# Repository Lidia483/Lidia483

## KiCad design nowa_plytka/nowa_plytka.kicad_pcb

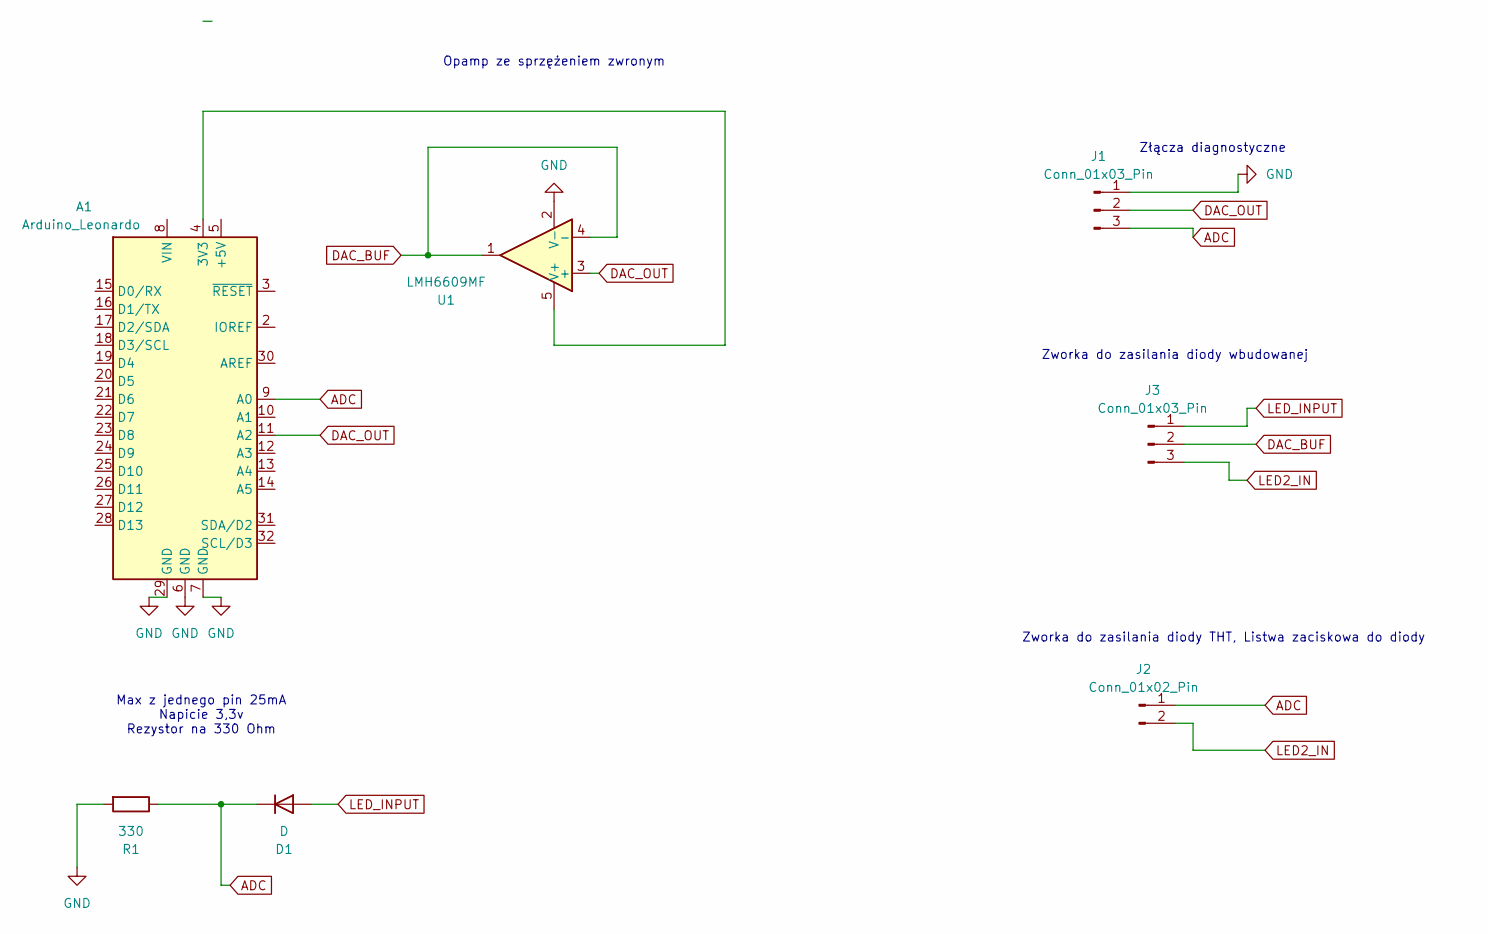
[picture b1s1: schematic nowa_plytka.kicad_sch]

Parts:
A1: Arduino_Leonardo; Arduino_UNO_R3
D1: D; D_1206_3216Metric
J1, J3: Conn_01x03_Pin; PinHeader_1x03_P2.54mm_Vertical
J2: Conn_01x02_Pin; PinHeader_1x02_P2.54mm_Vertical
R1: 330; R_1206_3216Metric
U1: LMH6609MF; SOT-23-5

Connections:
ADC: A1.9 (A0), D1.1 (K), J1.3, J2.1, R1.1
DAC_BUF: J3.2, U1.1, U1.4 (-)
DAC_OUT: A1.11 (A2), J1.2, U1.3 (+)
GND: A1.6 (GND), A1.7 (GND), A1.29 (GND), J1.1, R1.2, U1.2 (V-)
LED2_IN: J2.2, J3.3
LED_INPUT: D1.2 (A), J3.1
unnamed: A1.4 (3V3), U1.5 (V+)

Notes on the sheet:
Opamp ze sprzężeniem zwronym
Zworka do zasilania diody wbudowanej
Max z jednego pin 25mA Napicie 3,3v Rezystor na 330 Ohm
Złącza diagnostyczne
Zworka do zasilania diody THT, Listwa zaciskowa do diody

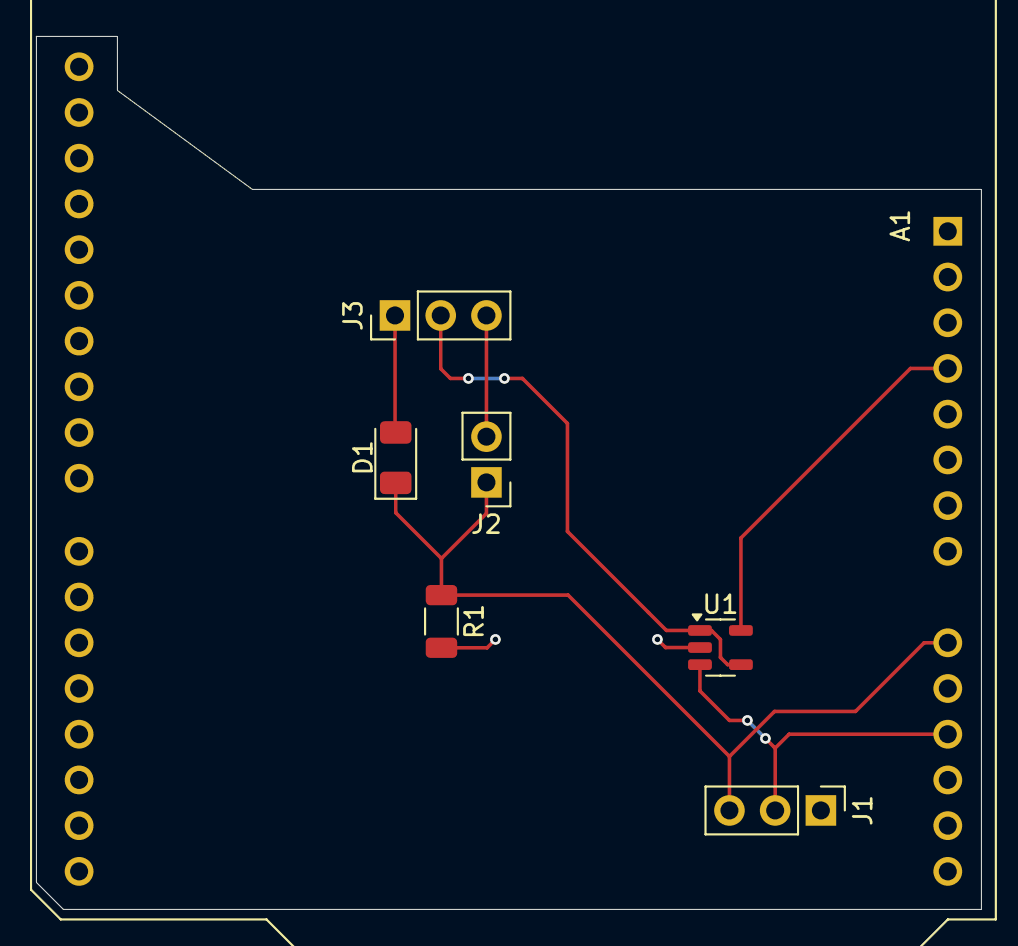
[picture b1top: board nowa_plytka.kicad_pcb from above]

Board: 2 copper layers, 52.5 x 48.5 mm, 7 parts (0 on the bottom side), 7 nets.

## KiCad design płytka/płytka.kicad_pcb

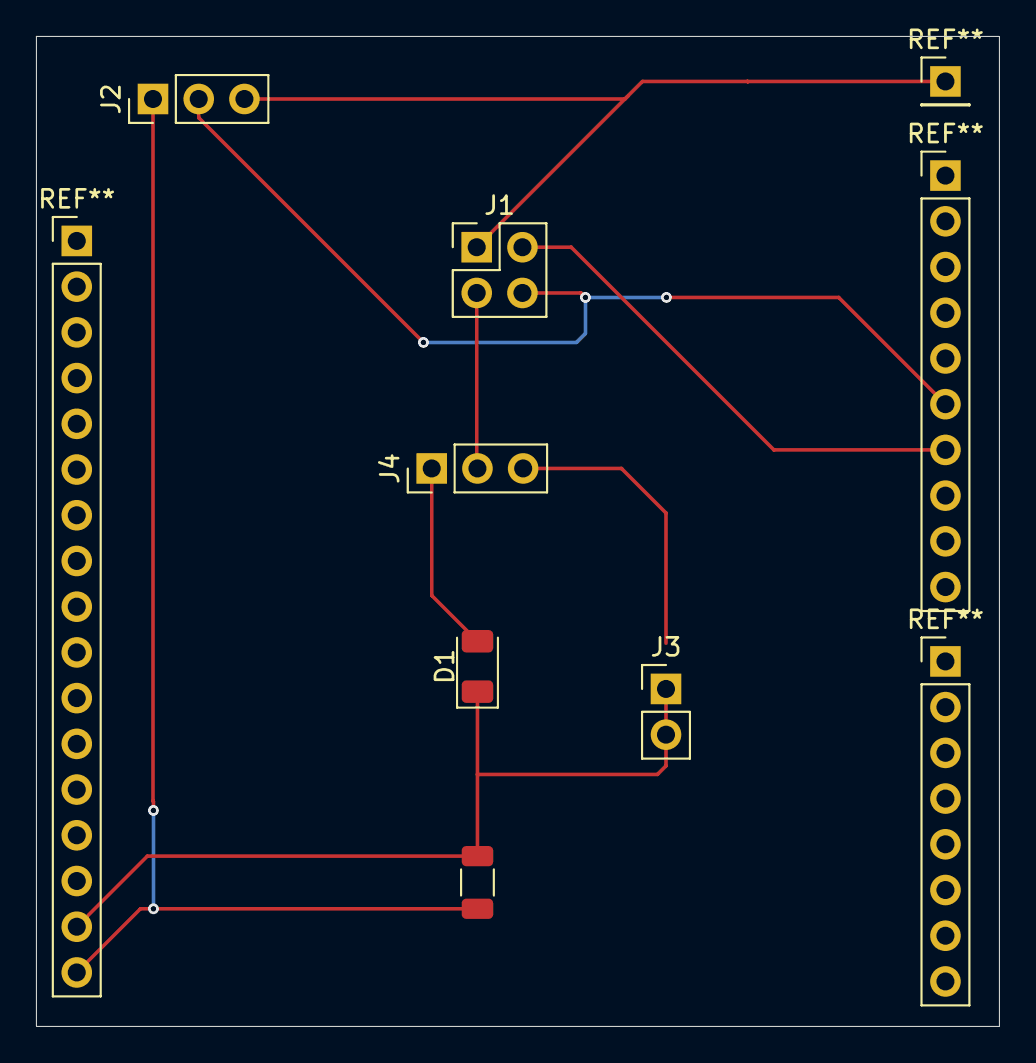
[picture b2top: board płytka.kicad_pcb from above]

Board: 2 copper layers, 53.5 x 55.0 mm, 6 parts (0 on the bottom side), 6 nets.

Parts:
D1: D; D_1206_3216Metric
J1: PinHeader_2x02_P2.54mm_Vertical
J2, J4: PinHeader_1x03_P2.54mm_Vertical
J3: PinHeader_1x02_P2.54mm_Vertical
R1: 100; R_1206_3216Metric

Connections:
ADC: D1.1 (K), J3.2, R1.1
DAC_OUT: J1.1, J2.3
GND: J2.1, R1.2
INPUT: D1.2 (A), J1.3, J4.1, J4.2
LED2_IN: J3.1, J4.3
OPAMP_OUT: J1.4, J2.2

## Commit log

2024-07-15 Implementacja estymatora Theil-kod
2024-07-15 Rename README.md to Theil-SenHAL.md
2024-09-10 Create hal (clock)
2024-09-10 Update and rename Theil-Sen.md to hal (gpio)
2024-09-10 Update and rename Theil-SenHAL.md to hal (uart)
2024-09-10 Create estimator
2024-09-10 Create main
2024-10-18 PLYTKA
2024-12-05 Create rdtrtyg
2024-12-05 Update rdtrtyg
